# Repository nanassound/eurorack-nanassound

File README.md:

# Nanas Sound's Eurorack Modules

Modules made by Nanas Sound.
- [Mini](https://github.com/bepitulaz/eurorack-nanassound/tree/main/Mini): USB-C power supply
- [Rohkem](https://github.com/bepitulaz/eurorack-nanassound/tree/main/Rohkem): 1x7 or 2x3 passive signal multiplier
- [Uksed](https://github.com/bepitulaz/eurorack-nanassound/tree/main/Uksed): 4-channels audio input module

## License

Hardware is licensed under [CC BY-SA 4.0](https://creativecommons.org/licenses/by-sa/4.0/).

By [Asep Bagja](https://www.asepbagja.com/)

Contact: [asep@nanas.ee](mailto:asep@nanas.ee)

© 2026 Nanas Sound OÜ

## Guidelines for derivative works

**Nanas Sound** is a business name of [Nanas Sound OÜ](https://ariregister.rik.ee/est/company/16028176/Nanas-Sound-OÜ).

You should not use Nanas Sound name, logo, or any other identifiers on your derivative works you create from files in this repository.

For example, your adaptation of Nanas Sound's Mini should be named "Strawberry Field - Mini Fruity" or similar.

You should include a visible license notice as required by the terms of the CC BY-SA 4.0 license.

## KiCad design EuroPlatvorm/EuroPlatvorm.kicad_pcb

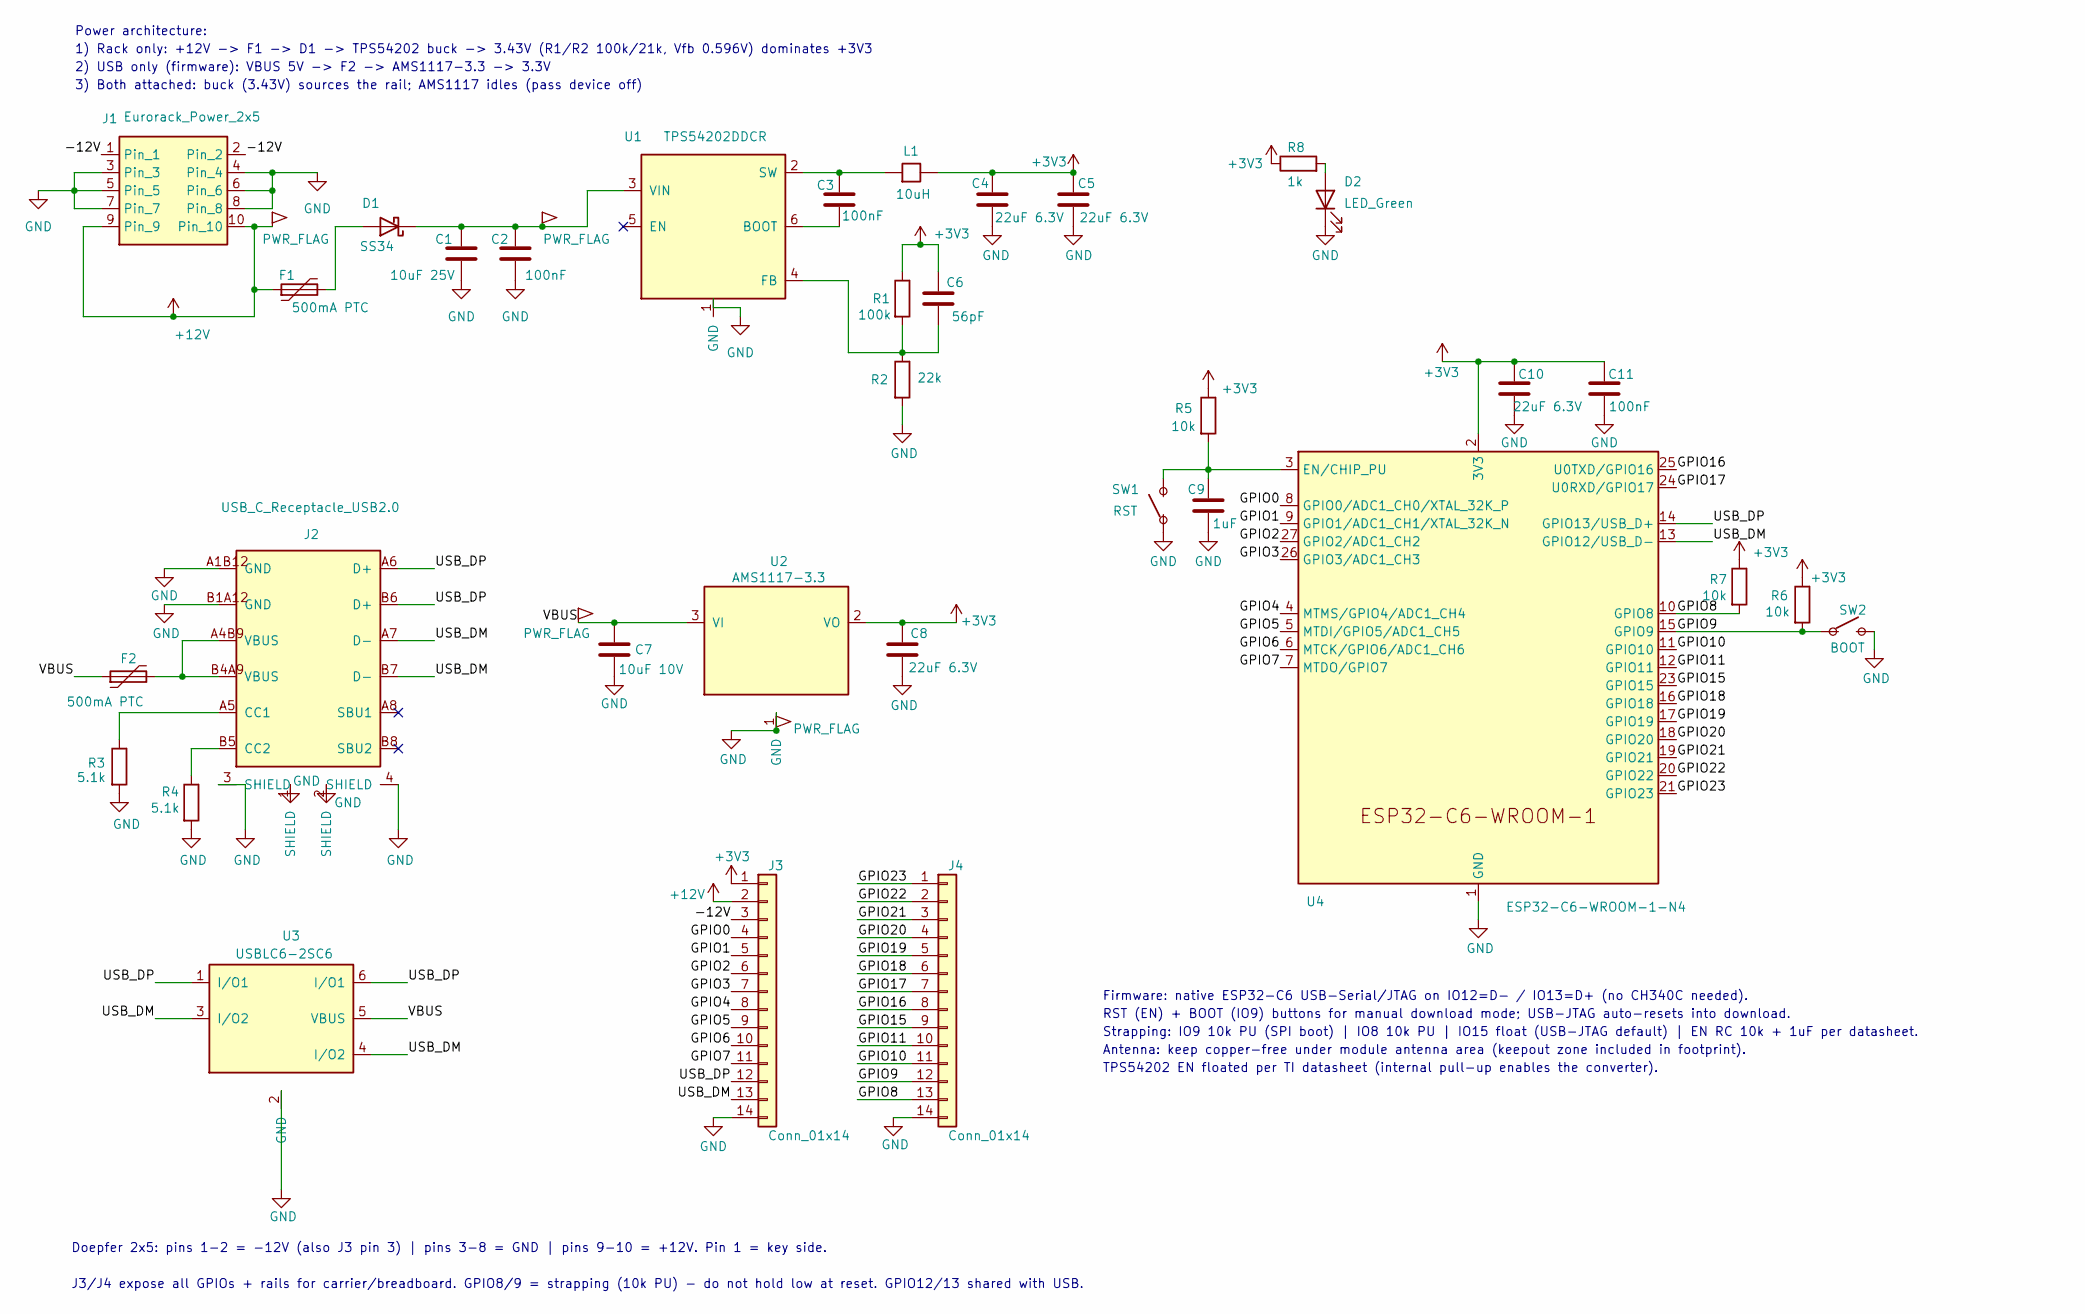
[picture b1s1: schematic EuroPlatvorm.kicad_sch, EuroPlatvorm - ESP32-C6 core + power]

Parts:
C1: 10uF 25V; C_1206_3216Metric; MPN CL31A106KAHNNNE; LCSC C9807
C2, C3: 100nF; C_0603_1608Metric; MPN CC0603KRX7R9BB104; LCSC C14663
C4, C5, C8, C10: 22uF 6.3V; C_0805_2012Metric; MPN CL21A226MQQNNNE; LCSC C5674
C6: 56pF; C_0603_1608Metric; MPN CL10C560JB8NNNC; LCSC C39148
C7: 10uF 10V; C_0805_2012Metric; MPN CL21A106KPCLQNC; LCSC C962097
C9: 1uF; C_0603_1608Metric; MPN CL10A105KO8NNNC; LCSC C1592
C11: 100nF; C_0402_1005Metric; MPN CL05B104KB5NNNC; LCSC C307331
D1: SS34; D_SMA; MPN SS34; LCSC C8678
D2: LED_Green; LED_0603_1608Metric; MPN XL-1608UGC-04; LCSC C965804
F1, F2: 500mA PTC; Fuse_1206_3216Metric; MPN 1206L050/30NR; LCSC C7542947
J1: Eurorack_Power_2x5; PinHeader_2x05_P2.54mm_Vertical; MPN PZ254V-12-10P; LCSC C492422
J2: USB_C_Receptacle_USB2.0; USB-C_SMD-TYPE-C-31-M-12_1; MPN TYPE-C-31-M-12; LCSC C165948
J3, J4: Conn_01x14; PinHeader_1x14_P2.54mm_Vertical; MPN 2.54-1x40P; LCSC C2337
L1: 10uH; IND-SMD_L6.0-W6.0; MPN YNR6045-100M; LCSC C341067
R1: 100k; R_0603_1608Metric; MPN 0603WAF1003T5E; LCSC C25803
R2: 22k; R_0603_1608Metric; MPN FRC0603F2202TS; LCSC C2907015
R3, R4: 5.1k; R_0603_1608Metric; MPN 0603WAF5101T5E; LCSC C23186
R5, R6, R7: 10k; R_0603_1608Metric; MPN FRC0603F1002TS; LCSC C2906982
R8: 1k; R_0603_1608Metric; MPN 0603WAF1001T5E; LCSC C21190
SW1: RST; SW_TS-1187A; MPN TS-1187A-B-A-B; LCSC C318884
SW2: BOOT; SW_TS-1187A; MPN TS-1187A-B-A-B; LCSC C318884
U1: TPS54202DDCR; SOT-23-6; MPN TPS54202DDCR; LCSC C191884
U2: AMS1117-3.3; SOT-223-3_TabPin2; MPN AMS1117-3.3; LCSC C6186
U3: USBLC6-2SC6; SOT-23-6; MPN USBLC6-2SC6; LCSC C7519
U4: ESP32-C6-WROOM-1-N4; ESP32-C6-WROOM-1; MPN ESP32-C6-WROOM-1-N4; LCSC C6034714

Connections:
+3V3: C4.1, C5.1, C6.1, C8.1, C10.2, C11.2, J3.1, L1.2, R1.1, R5.1, R6.1, R7.1, R8.1, U2.2 (VO), U4.2 (3V3)
+12V: F1.1, J1.9, J1.10, J3.2
/-12V: J1.1, J1.2, J3.3
/GPIO0: J3.4, U4.8 (GPIO0/ADC1_CH0/XTAL_32K_P)
/GPIO1: J3.5, U4.9 (GPIO1/ADC1_CH1/XTAL_32K_N)
/GPIO2: J3.6, U4.27 (GPIO2/ADC1_CH2)
/GPIO3: J3.7, U4.26 (GPIO3/ADC1_CH3)
/GPIO4: J3.8, U4.4 (MTMS/GPIO4/ADC1_CH4)
/GPIO5: J3.9, U4.5 (MTDI/GPIO5/ADC1_CH5)
/GPIO6: J3.10, U4.6 (MTCK/GPIO6/ADC1_CH6)
/GPIO7: J3.11, U4.7 (MTDO/GPIO7)
/GPIO8: J4.13, R7.2, U4.10 (GPIO8)
/GPIO9: J4.12, R6.2, SW2.1, U4.15 (GPIO9)
/GPIO10: J4.11, U4.11 (GPIO10)
/GPIO11: J4.10, U4.12 (GPIO11)
/GPIO15: J4.9, U4.23 (GPIO15)
/GPIO16: J4.8, U4.25 (U0TXD/GPIO16)
/GPIO17: J4.7, U4.24 (U0RXD/GPIO17)
/GPIO18: J4.6, U4.16 (GPIO18)
/GPIO19: J4.5, U4.17 (GPIO19)
/GPIO20: J4.4, U4.18 (GPIO20)
/GPIO21: J4.3, U4.19 (GPIO21)
/GPIO22: J4.2, U4.20 (GPIO22)
/GPIO23: J4.1, U4.21 (GPIO23)
/USB_DM: J2.A7 (D-), J2.B7 (D-), J3.13, U3.3 (I/O2), U3.4 (I/O2), U4.13 (GPIO12/USB_D-)
/USB_DP: J2.A6 (D+), J2.B6 (D+), J3.12, U3.1 (I/O1), U3.6 (I/O1), U4.14 (GPIO13/USB_D+)
/VBUS: C7.1, F2.1, U2.3 (VI), U3.5 (VBUS)
GND: C1.2, C2.2, C4.2, C5.2, C7.2, C8.2, C9.2, C10.1, C11.1, D2.1 (K), J1.3, J1.4, J1.5, J1.6, J1.7, J1.8, J2.1 (SHIELD), J2.2 (SHIELD), J2.3 (SHIELD), J2.4 (SHIELD), J2.A1B12 (GND), J2.B1A12 (GND), J3.14, J4.14, R2.2, R3.2, R4.2, SW1.1, SW2.2, U1.1 (GND), U2.1 (GND), U3.2 (GND), U4.1 (GND), U4.28 (GND), U4.29 (GND)
unnamed: D1.2 (A), F1.2
unnamed: C1.1, C2.1, D1.1 (K), U1.3 (VIN)
unnamed: D2.2 (A), R8.2
unnamed: F2.2, J2.A4B9 (VBUS), J2.B4A9 (VBUS)
unnamed: J2.A5 (CC1), R3.1
unnamed: J2.B5 (CC2), R4.1
unnamed: C3.2, U1.6 (BOOT)
unnamed: C6.2, R1.2, R2.1, U1.4 (FB)
unnamed: C3.1, L1.1, U1.2 (SW)
unnamed: C9.1, R5.2, SW1.2, U4.3 (EN/CHIP_PU)

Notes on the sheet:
Strapping: IO9 10k PU (SPI boot) | IO8 10k PU | IO15 float (USB-JTAG default) | EN RC 10k + 1uF per datasheet.
Doepfer 2x5: pins 1-2 = -12V (also J3 pin 3) | pins 3-8 = GND | pins 9-10 = +12V. Pin 1 = key side.
J3/J4 expose all GPIOs + rails for carrier/breadboard. GPIO8/9 = strapping (10k PU) - do not hold low at reset. GPIO12/13 shared with USB.
Firmware: native ESP32-C6 USB-Serial/JTAG on IO12=D- / IO13=D+ (no CH340C needed).
RST (EN) + BOOT (IO9) buttons for manual download mode; USB-JTAG auto-resets into download.
Power architecture:
2) USB only (firmware): VBUS 5V -> F2 -> AMS1117-3.3 -> 3.3V
3) Both attached: buck (3.43V) sources the rail; AMS1117 idles (pass device off)
TPS54202 EN floated per TI datasheet (internal pull-up enables the converter).
Antenna: keep copper-free under module antenna area (keepout zone included in footprint).
1) Rack only: +12V -> F1 -> D1 -> TPS54202 buck -> 3.43V (R1/R2 100k/21k, Vfb 0.596V) dominates +3V3

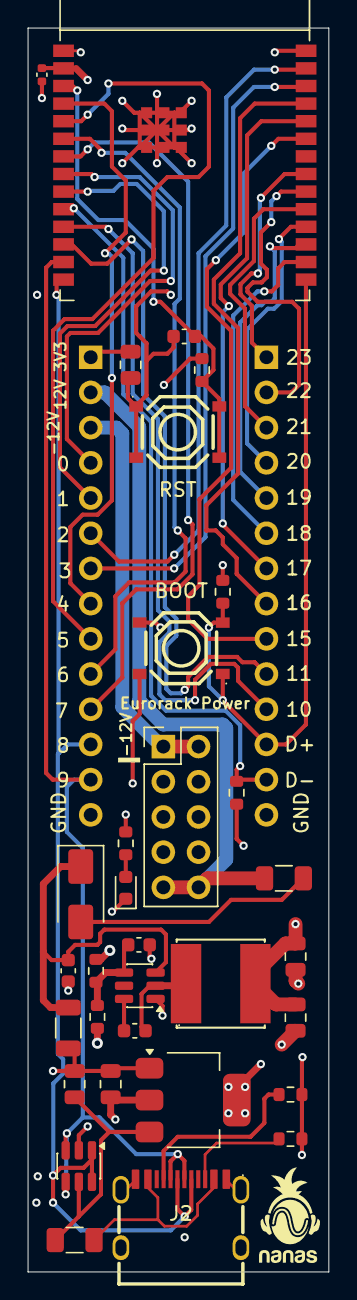
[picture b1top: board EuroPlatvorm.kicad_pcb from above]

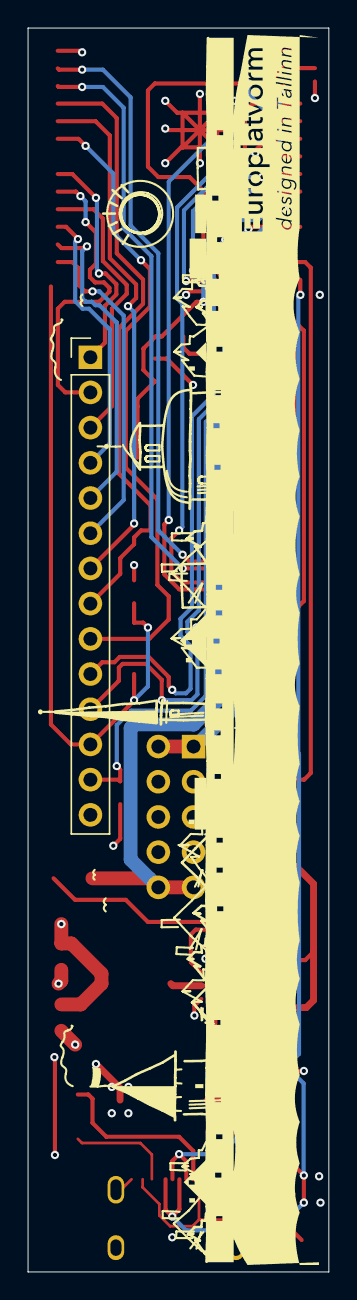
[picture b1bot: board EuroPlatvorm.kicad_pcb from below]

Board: 4 copper layers, 21.7 x 89.8 mm, 34 parts (2 on the bottom side), 38 nets.

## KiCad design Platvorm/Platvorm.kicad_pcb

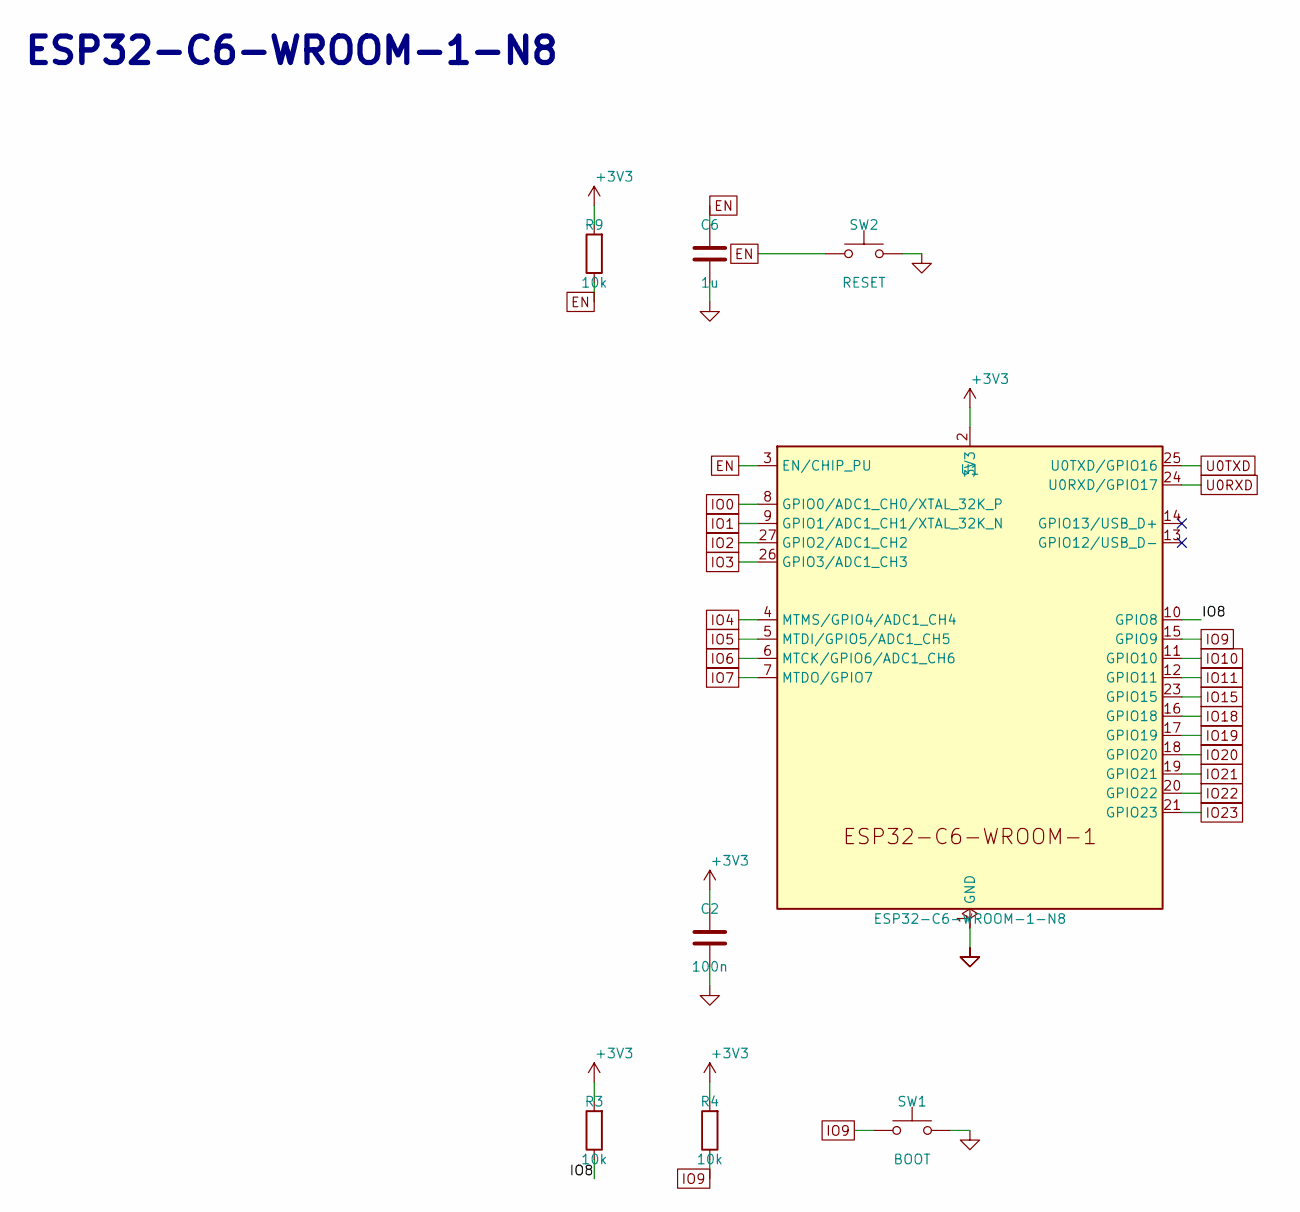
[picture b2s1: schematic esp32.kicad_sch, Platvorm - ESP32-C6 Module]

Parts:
C2: 100n; C_0402_1005Metric; MPN CL05B104KO5NNNC; LCSC C1525
C6: 1u; C_0402_1005Metric; MPN CL05A105KA5NNNC; LCSC C52923
R3, R4, R9: 10k; R_0402_1005Metric; MPN RC0402FR-0710KL; LCSC C25744
SW1: BOOT; SW_TS-1187A; MPN TS-1187A-B-A-B; LCSC C318884
SW2: RESET; SW_TS-1187A; MPN TS-1187A-B-A-B; LCSC C318884
U1: ESP32-C6-WROOM-1-N8; ESP32-C6-WROOM-1; MPN ESP32-C6-WROOM-1-N8; LCSC C5366877

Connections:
/ESP32-C6 Module/IO8: R3.1, U1.10 (GPIO8)
EN: C6.1, R9.1, SW2.1, U1.3 (EN/CHIP_PU); also elsewhere on the board
GND: C2.2, C6.2, SW1.2, SW2.2, U1.1 (GND), U1.28 (GND), U1.29 (GND); also elsewhere on the board
IO0: U1.8 (GPIO0/ADC1_CH0/XTAL_32K_P); also elsewhere on the board
IO1: U1.9 (GPIO1/ADC1_CH1/XTAL_32K_N); also elsewhere on the board
IO2: U1.27 (GPIO2/ADC1_CH2); also elsewhere on the board
IO3: U1.26 (GPIO3/ADC1_CH3); also elsewhere on the board
IO4: U1.4 (MTMS/GPIO4/ADC1_CH4); also elsewhere on the board
IO5: U1.5 (MTDI/GPIO5/ADC1_CH5); also elsewhere on the board
IO6: U1.6 (MTCK/GPIO6/ADC1_CH6); also elsewhere on the board
IO7: U1.7 (MTDO/GPIO7); also elsewhere on the board
IO9: R4.1, SW1.1, U1.15 (GPIO9); also elsewhere on the board
IO10: U1.11 (GPIO10); also elsewhere on the board
IO11: U1.12 (GPIO11); also elsewhere on the board
IO15: U1.23 (GPIO15); also elsewhere on the board
IO18: U1.16 (GPIO18); also elsewhere on the board
IO19: U1.17 (GPIO19); also elsewhere on the board
IO20: U1.18 (GPIO20); also elsewhere on the board
IO21: U1.19 (GPIO21); also elsewhere on the board
IO22: U1.20 (GPIO22); also elsewhere on the board
IO23: U1.21 (GPIO23); also elsewhere on the board
U0RXD: U1.24 (U0RXD/GPIO17); also elsewhere on the board
U0TXD: U1.25 (U0TXD/GPIO16); also elsewhere on the board

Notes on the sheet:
ESP32-C6-WROOM-1-N8

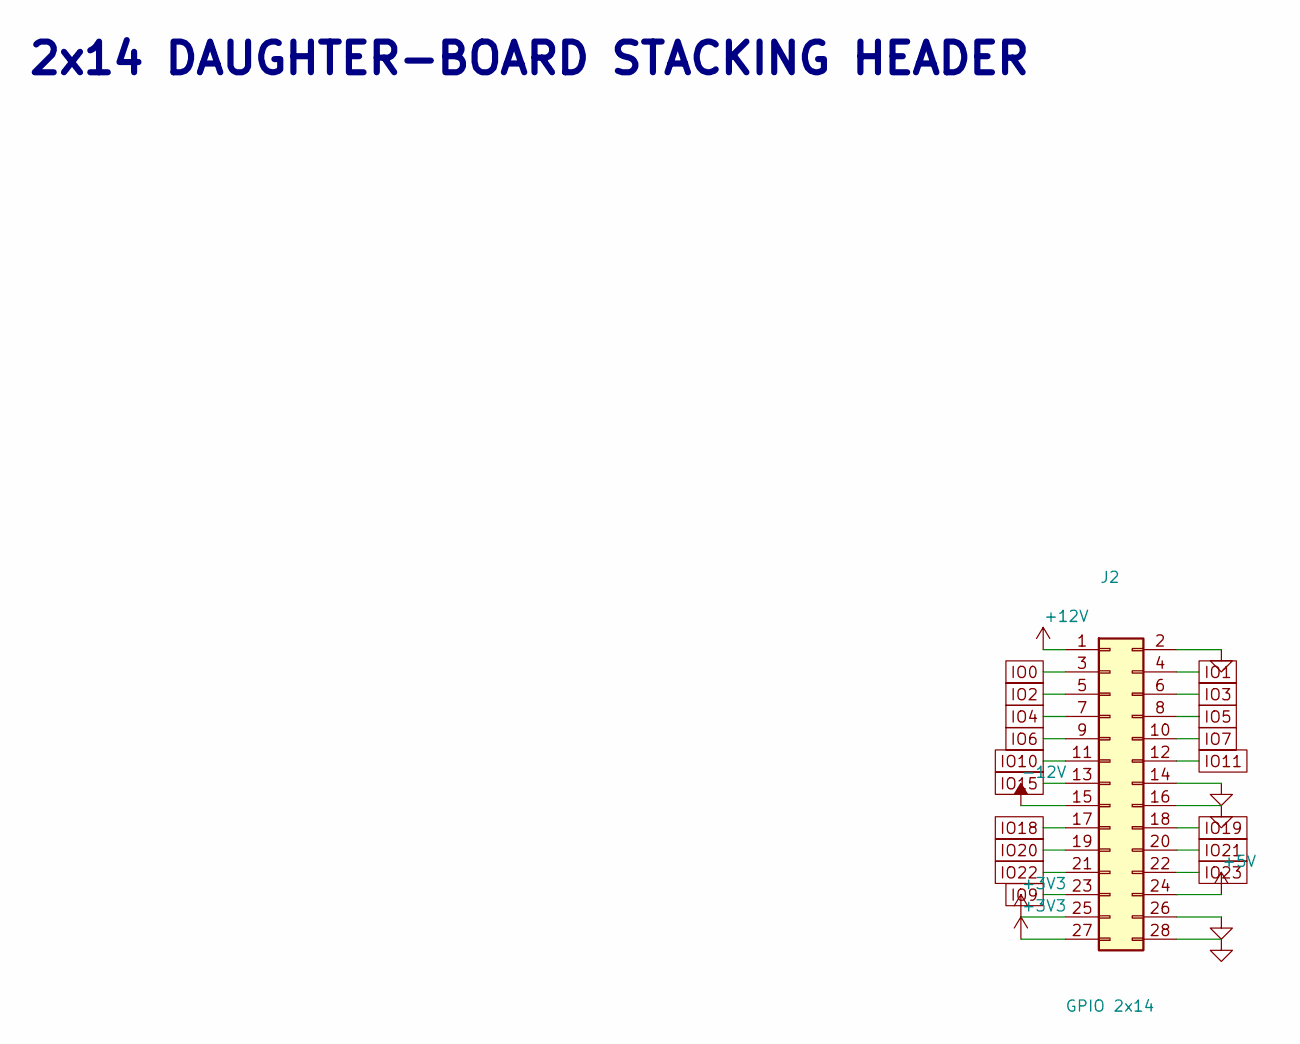
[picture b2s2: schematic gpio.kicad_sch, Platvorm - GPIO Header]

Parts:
J2: GPIO 2x14; PinHeader_2x14_P2.54mm_Vertical; MPN PZ254V-12-28P; LCSC C22465888

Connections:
GND: J2.2, J2.14, J2.16, J2.26, J2.28; also elsewhere on the board
IO0: J2.3; also elsewhere on the board
IO1: J2.4; also elsewhere on the board
IO2: J2.5; also elsewhere on the board
IO3: J2.6; also elsewhere on the board
IO4: J2.7; also elsewhere on the board
IO5: J2.8; also elsewhere on the board
IO6: J2.9; also elsewhere on the board
IO7: J2.10; also elsewhere on the board
IO9: J2.23; also elsewhere on the board
IO10: J2.11; also elsewhere on the board
IO11: J2.12; also elsewhere on the board
IO15: J2.13; also elsewhere on the board
IO18: J2.17; also elsewhere on the board
IO19: J2.18; also elsewhere on the board
IO20: J2.19; also elsewhere on the board
IO21: J2.20; also elsewhere on the board
IO22: J2.21; also elsewhere on the board
IO23: J2.22; also elsewhere on the board

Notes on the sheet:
2x14 DAUGHTER-BOARD STACKING HEADER

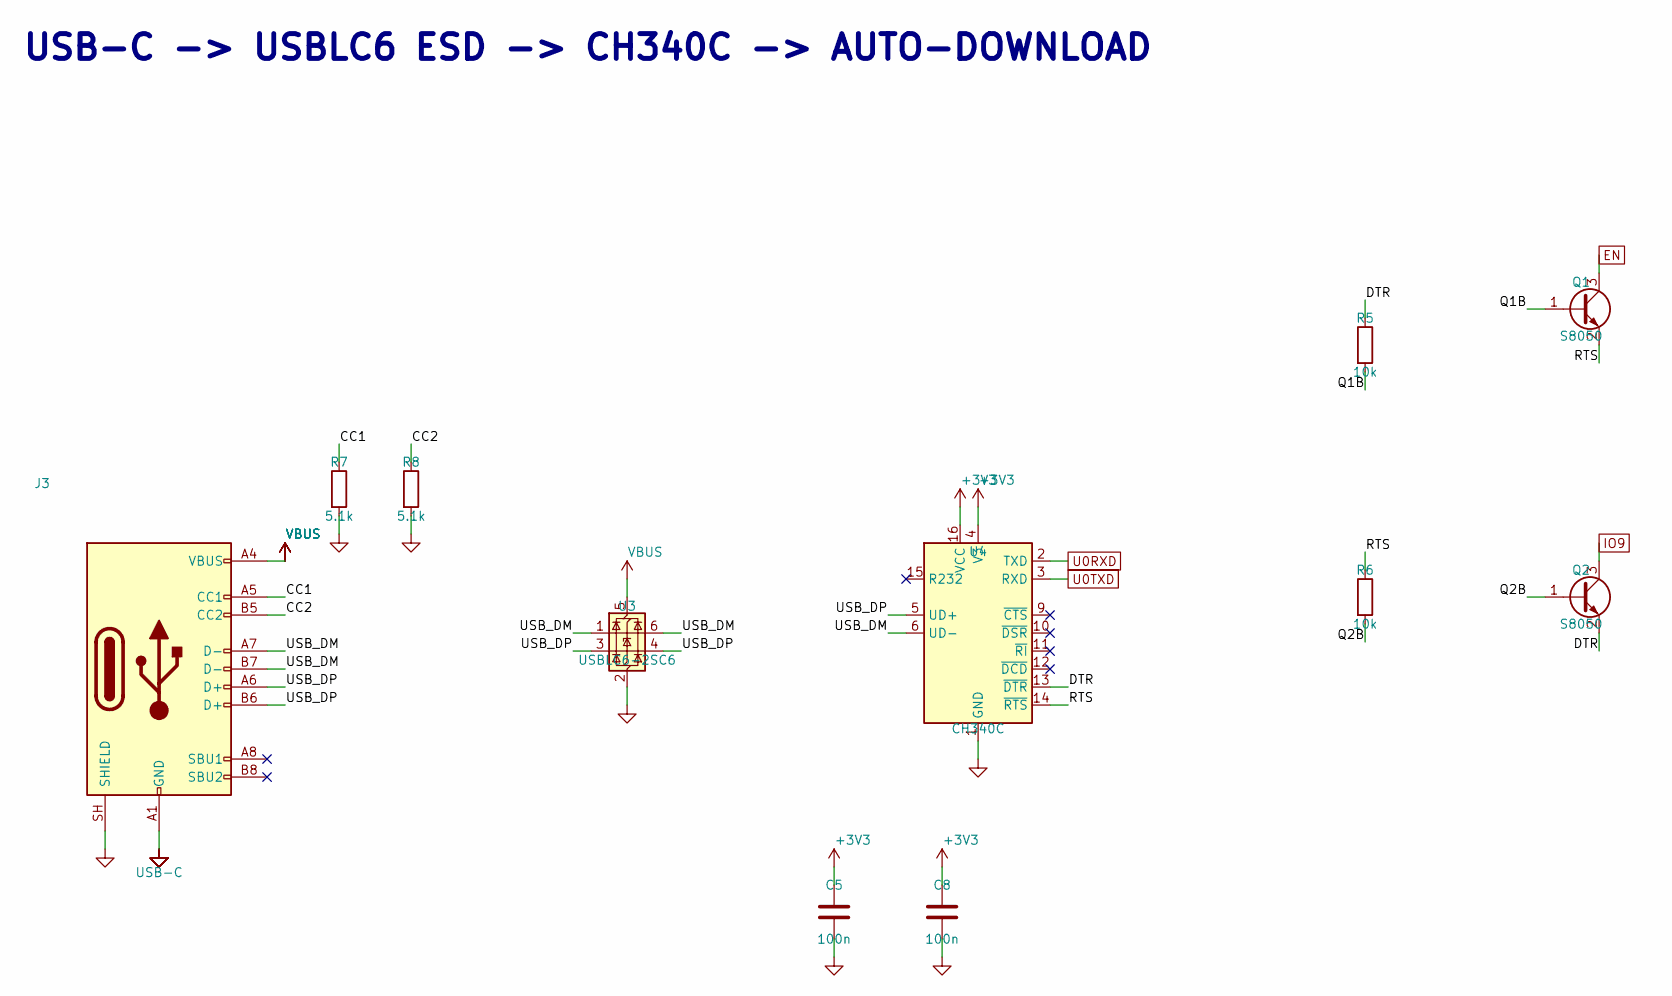
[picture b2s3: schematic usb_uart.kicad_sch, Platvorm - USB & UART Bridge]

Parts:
C5, C8: 100n; C_0402_1005Metric; MPN CL05B104KO5NNNC; LCSC C1525
J3: USB-C; USB-C_SMD-TYPE-C-31-M-12_1; MPN TYPE-C-31-M-12; LCSC C165948
Q1, Q2: S8050; SOT-23; MPN S8050; LCSC C2146
R5, R6: 10k; R_0402_1005Metric; MPN RC0402FR-0710KL; LCSC C25744
R7, R8: 5.1k; R_0402_1005Metric; MPN RC0402FR-075K1L; LCSC C25905
U3: USBLC6-2SC6; SOT-23-6; MPN USBLC6-2SC6; LCSC C2687116
U4: CH340C; SOP-16_4.4x10.4mm_P1.27mm; MPN CH340C; LCSC C84681

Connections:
/USB & UART Bridge/CC1: J3.A5 (CC1), R7.1
/USB & UART Bridge/CC2: J3.B5 (CC2), R8.1
/USB & UART Bridge/DTR: Q2.2 (E), R5.1, U4.13 (~DTR)
/USB & UART Bridge/Q1B: Q1.1 (B), R5.2
/USB & UART Bridge/Q2B: Q2.1 (B), R6.2
/USB & UART Bridge/RTS: Q1.2 (E), R6.1, U4.14 (~RTS)
/USB & UART Bridge/USB_DM: J3.A7 (D-), J3.B7 (D-), U3.1 (I/O1), U3.6 (I/O1), U4.6 (UD-)
/USB & UART Bridge/USB_DP: J3.A6 (D+), J3.B6 (D+), U3.3 (I/O2), U3.4 (I/O2), U4.5 (UD+)
EN: Q1.3 (C); also elsewhere on the board
GND: C5.2, C8.2, J3.1, J3.2, J3.3, J3.4, J3.A1 (GND), J3.A1B12, J3.A12 (GND), J3.B1 (GND), J3.B1A12, J3.B12 (GND), J3.SH (SHIELD), R7.2, R8.2, U3.2 (GND), U4.1 (GND); also elsewhere on the board
IO9: Q2.3 (C); also elsewhere on the board
U0RXD: U4.2 (TXD); also elsewhere on the board
U0TXD: U4.3 (RXD); also elsewhere on the board

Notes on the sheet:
USB-C -> USBLC6 ESD -> CH340C -> AUTO-DOWNLOAD

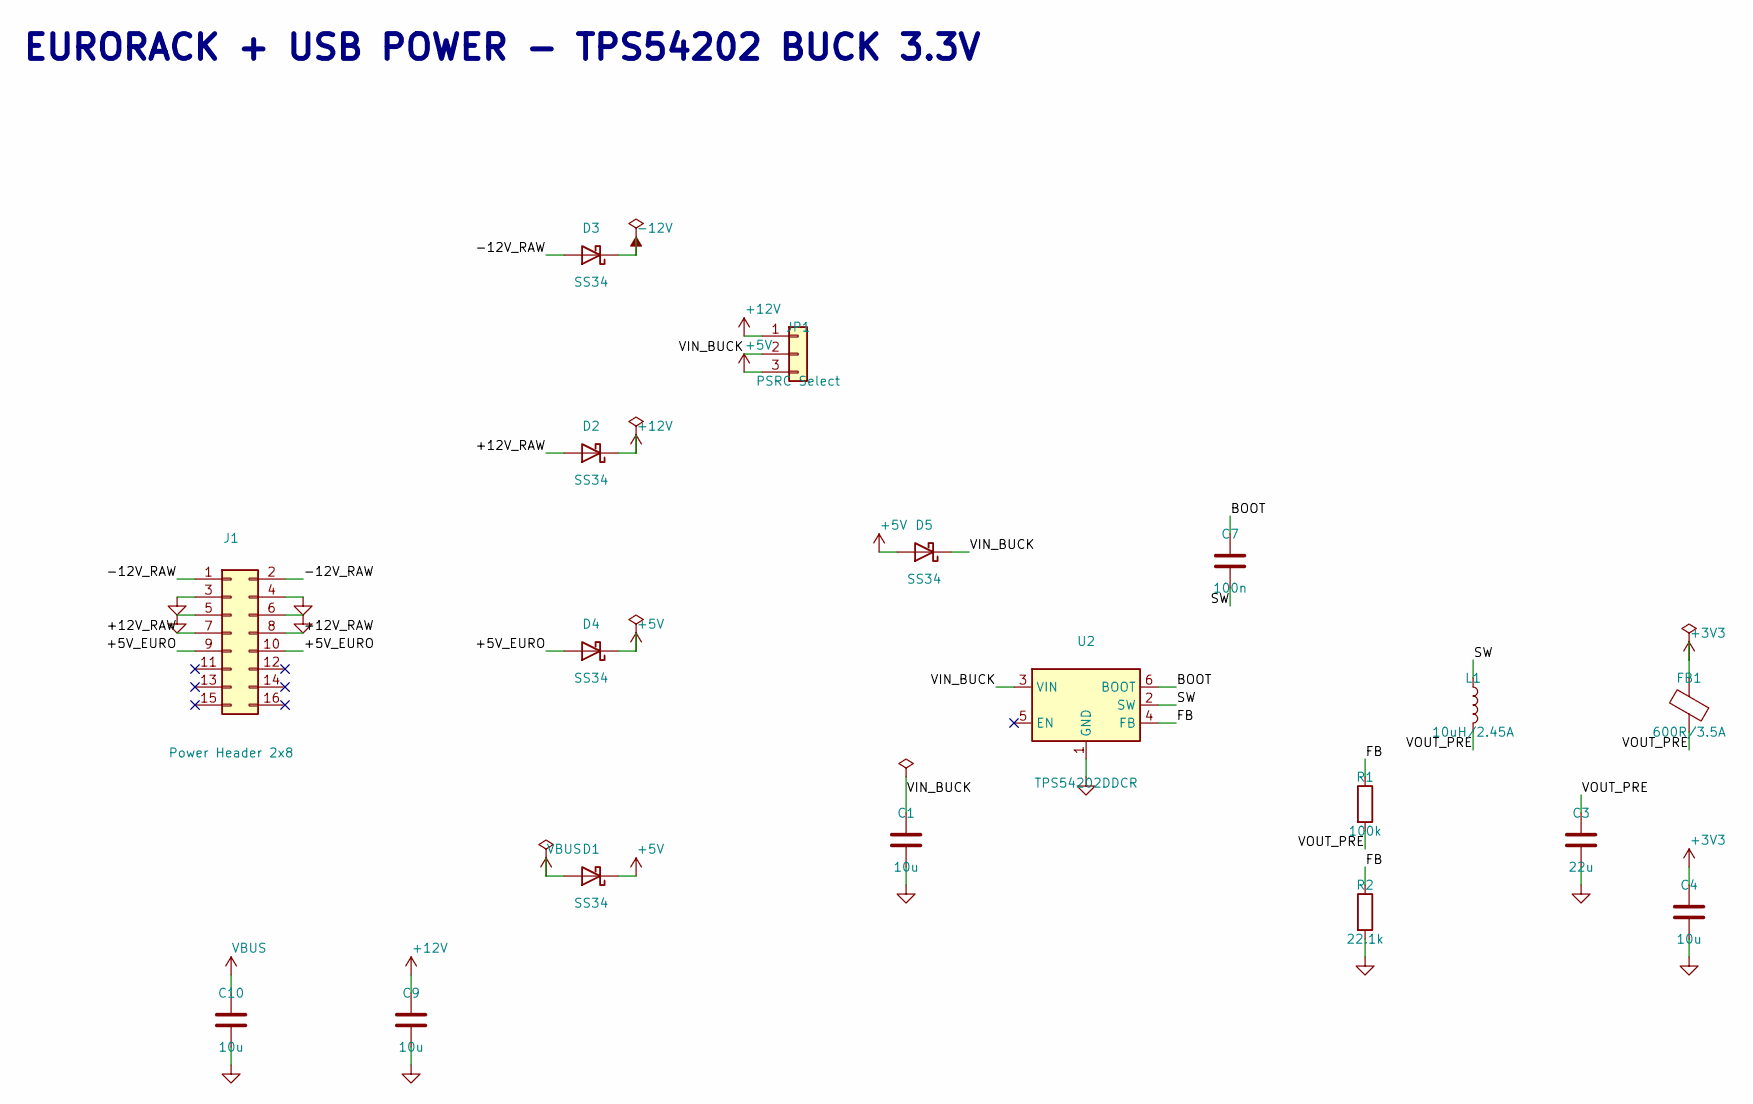
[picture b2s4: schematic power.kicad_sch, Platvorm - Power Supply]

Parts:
C1, C4, C9, C10: 10u; C_0805_2012Metric; MPN CL21A106KAYNNNE; LCSC C15850
C3: 22u; C_0805_2012Metric; MPN CL21A226MAQNNNE; LCSC C45783
C7: 100n; C_0402_1005Metric; MPN CL05B104KO5NNNC; LCSC C1525
D1, D2, D3, D4, D5: SS34; D_SMA; MPN SS34; LCSC C8678
FB1: 600R/3.5A; L_0805_2012Metric; MPN BLM21PG600SN1D; LCSC C18305
J1: Power Header 2x8; PinHeader_2x08_P2.54mm_Vertical; MPN PZ254V-12-16P; LCSC C492425
JP1: PSRC Select; PinHeader_1x03_P2.54mm_Vertical; MPN DZ254R-11-03-63; LCSC C2935909
L1: 10uH/2.45A; IND-SMD_L6.0-W6.0; MPN YNR6045-100M; LCSC C341067
R1: 100k; R_0402_1005Metric; MPN RC0402FR-07100KL; LCSC C25741
R2: 22.1k; R_0402_1005Metric; MPN RC0402FR-0722K1L; LCSC C43473
U2: TPS54202DDCR; SOT-23-6; MPN TPS54202DDCR; LCSC C191884

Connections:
/Power Supply/+5V_EURO: D4.2 (A), J1.9, J1.10
/Power Supply/+12V_RAW: D2.2 (A), J1.7, J1.8
/Power Supply/-12V_RAW: D3.2 (A), J1.1, J1.2
/Power Supply/BOOT: C7.1, U2.6 (BOOT)
/Power Supply/FB: R1.1, R2.1, U2.4 (FB)
/Power Supply/SW: C7.2, L1.1, U2.2 (SW)
/Power Supply/VOUT_PRE: C3.1, FB1.1, L1.2, R1.2
GND: C1.2, C3.2, C4.2, C9.2, C10.2, J1.3, J1.4, J1.5, J1.6, R2.2, U2.1 (GND); also elsewhere on the board

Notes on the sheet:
EURORACK + USB POWER - TPS54202 BUCK 3.3V

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
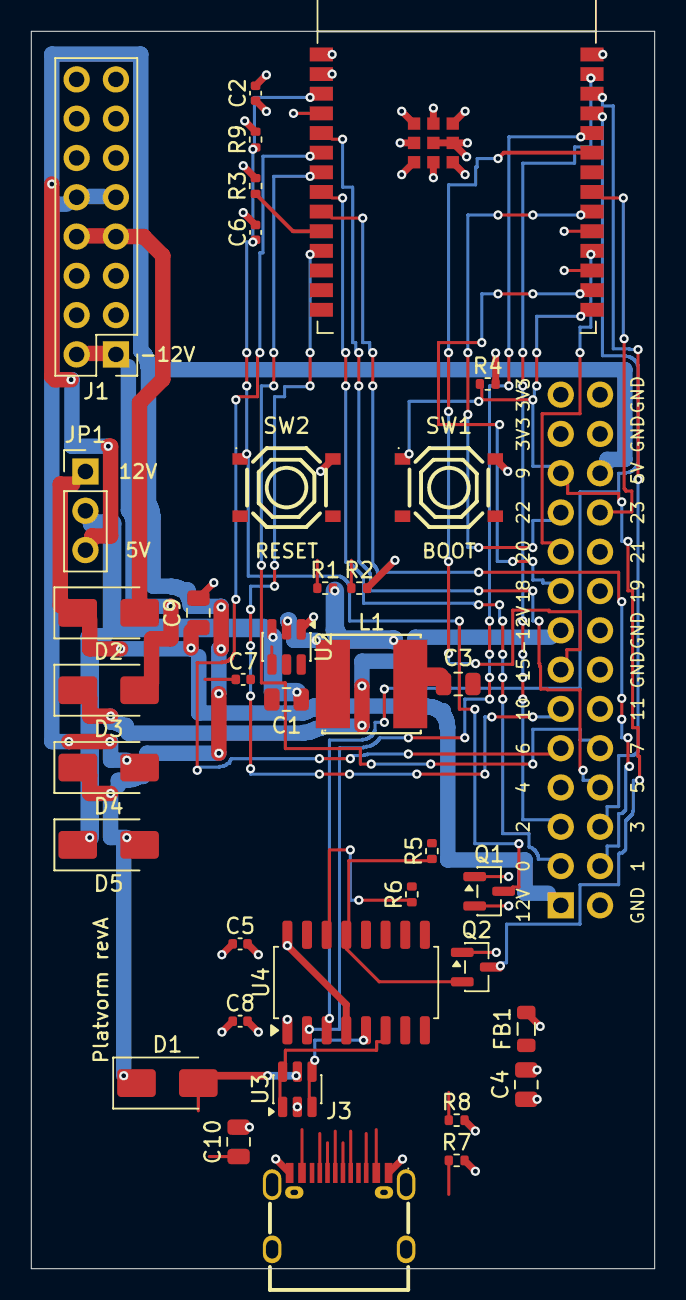
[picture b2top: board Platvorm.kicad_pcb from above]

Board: 4 copper layers, 40.3 x 80.0 mm, 38 parts (1 on the bottom side), 44 nets.

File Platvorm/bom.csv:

"Designator","Comment","Value","Footprint","JLCPCB Part #"
"U1","ESP32-C6-WROOM-1-N8 WiFi6/BLE/802.15.4 module, 8MB flash","ESP32-C6-WROOM-1-N8","platvorm_custom:ESP32-C6-WROOM-1","C5366877"
"U2","TPS54202DDCR buck 4.5-28V 2A 500kHz (3.3V out via R1/R2)","TPS54202DDCR","Package_TO_SOT_SMD:SOT-23-6","C191884"
"U3","USBLC6-2SC6 USB ESD protection","USBLC6-2SC6","Package_TO_SOT_SMD:SOT-23-6","C2687116"
"U4","CH340C USB-UART bridge, internal osc, 3.3V","CH340C","Package_SO:SOP-16_4.4x10.4mm_P1.27mm","C84681"
"FB1","BLM21PG600SN1D ferrite bead 600R@100MHz 3.5A (ripple filter)","600R/3.5A","Inductor_SMD:L_0805_2012Metric","C18305"
"L1","YNR6045-100M 10uH magnetically shielded, Isat 2.45A (replaces unshielded C5289420)","10uH","platvorm_custom:IND-SMD_L6.0-W6.0","C341067"
"D1","SS34: USB VBUS -> +5V rail","SS34","Diode_SMD:D_SMA","C8678"
"D2","SS34: eurorack +12V series protection","SS34","Diode_SMD:D_SMA","C8678"
"D3","SS34: eurorack -12V series protection (reversed)","SS34","Diode_SMD:D_SMA","C8678"
"D4","SS34: eurorack +5V -> +5V rail","SS34","Diode_SMD:D_SMA","C8678"
"D5","SS34: +5V -> VIN_BUCK (USB-only power backup when JP1=12V)","SS34","Diode_SMD:D_SMA","C8678"
"Q1","S8050 NPN: DTR/RTS -> EN auto-reset","S8050","Package_TO_SOT_SMD:SOT-23","C2146"
"Q2","S8050 NPN: DTR/RTS -> IO9 auto-boot","S8050","Package_TO_SOT_SMD:SOT-23","C2146"
"R1","FB divider high (Vout = 0.6*(1+100k/22.1k) = 3.31V)","100k","Resistor_SMD:R_0402_1005Metric","C25741"
"R2","FB divider low","22.1k","Resistor_SMD:R_0402_1005Metric","C43473"
"R3","IO8 strap pull-up","10k","Resistor_SMD:R_0402_1005Metric","C25744"
"R4","IO9/BOOT pull-up","10k","Resistor_SMD:R_0402_1005Metric","C25744"
"R5","Q1 base (DTR), ESP-Prog topology","10k","Resistor_SMD:R_0402_1005Metric","C25744"
"R6","Q2 base (RTS), ESP-Prog topology","10k","Resistor_SMD:R_0402_1005Metric","C25744"
"R7","USB CC1 pull-down 5.1k","5.1k","Resistor_SMD:R_0402_1005Metric","C25905"
"R8","USB CC2 pull-down 5.1k","5.1k","Resistor_SMD:R_0402_1005Metric","C25905"
"R9","EN pull-up","10k","Resistor_SMD:R_0402_1005Metric","C25744"
"C1","Buck input cap 25V X5R","10u","Capacitor_SMD:C_0805_2012Metric","C15850"
"C3","Buck output cap 25V X5R","22u","Capacitor_SMD:C_0805_2012Metric","C45783"
"C4","+3V3 bulk after ferrite bead","10u","Capacitor_SMD:C_0805_2012Metric","C15850"
"C9","+12V rail bulk 25V X5R","10u","Capacitor_SMD:C_0805_2012Metric","C15850"
"C10","VBUS bulk 25V X5R","10u","Capacitor_SMD:C_0805_2012Metric","C15850"
"C2","U1 decoupling","100n","Capacitor_SMD:C_0402_1005Metric","C1525"
"C5","U4 CH340C VCC decoupling","100n","Capacitor_SMD:C_0402_1005Metric","C1525"
"C7","U2 TPS54202 BOOT cap","100n","Capacitor_SMD:C_0402_1005Metric","C1525"
"C8","U4 CH340C V3 decoupling (V3 tied to VCC, 3.3V op)","100n","Capacitor_SMD:C_0402_1005Metric","C1525"
"C6","EN reset delay","1u","Capacitor_SMD:C_0402_1005Metric","C52923"
"SW1","BOOT button (IO9)","TS-1187A","platvorm_custom:SW_TS-1187A","C318884"
"SW2","RESET button (EN)","TS-1187A","platvorm_custom:SW_TS-1187A","C318884"
"J1","PZ254V-12-16P eurorack power 2x8 (pin1=-12V, red stripe)","Power 2x8","Connector_PinHeader_2.54mm:PinHeader_2x08_P2.54mm_Vertical","C492425"
"J2","PZ254V-12-28P daughter-board header 2x14 (see design doc)","GPIO 2x14","Connector_PinHeader_2.54mm:PinHeader_2x14_P2.54mm_Vertical","C22465888"
"JP1","DZ254R-11-03-63 buck source jumper: pin1-2=12V, pin2-3=5V","PSRC Select","Connector_PinHeader_2.54mm:PinHeader_1x03_P2.54mm_Vertical","C2935909"
"J3","TYPE-C-31-M-12 USB-C 16P (power + programming)","USB-C","platvorm_custom:USB-C_SMD-TYPE-C-31-M-12_1","C165948"
